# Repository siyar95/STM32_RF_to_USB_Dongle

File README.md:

# RF to USB Dongle – STM32L432 + nRF24L01

This project is a compact **RF-to-USB dongle** built using an **STM32L432KBU** microcontroller and an **nRF24L01** 2.4 GHz transceiver module.  
The device receives RF data wirelessly and transmits it to a host computer over USB.

## 🔧 Features

- **MCU**: STM32L432KBU (ARM Cortex-M4, ultra-low power)
- **RF Module**: nRF24L01 (2.4 GHz transceiver)
- **USB Interface**: Native USB device for communication with PC or host
- **SPI Interface**: Used to communicate with the nRF24L01
- **Low Power Operation**: Suitable for battery-powered wireless systems
- **Compact Design**: USB dongle-style form factor

## 🎯 Applications

- Wireless data receiver (e.g., for sensors, remotes)
- USB dongle for custom RF communication protocols
- PC bridge for STM32-based RF networks
- Debugging/logging tool for embedded wireless systems

## 🧱 PCB Details

- 4-layer PCB
- **Micro-USB (Type B)** connector
- On-board 3.3V LDO regulator for nRF24L01 and STM32
- SMA antenna

## 🧱 PCB Stackup

This project uses a 4-layer PCB for better signal integrity and power distribution:

1. **Top Layer (Layer 1)** – Signal  
2. **Inner Layer 1 (Layer 2)** – Ground (GND)  
3. **Inner Layer 2 (Layer 3)** – 3.3V Power Plane  
4. **Bottom Layer (Layer 4)** – Signal

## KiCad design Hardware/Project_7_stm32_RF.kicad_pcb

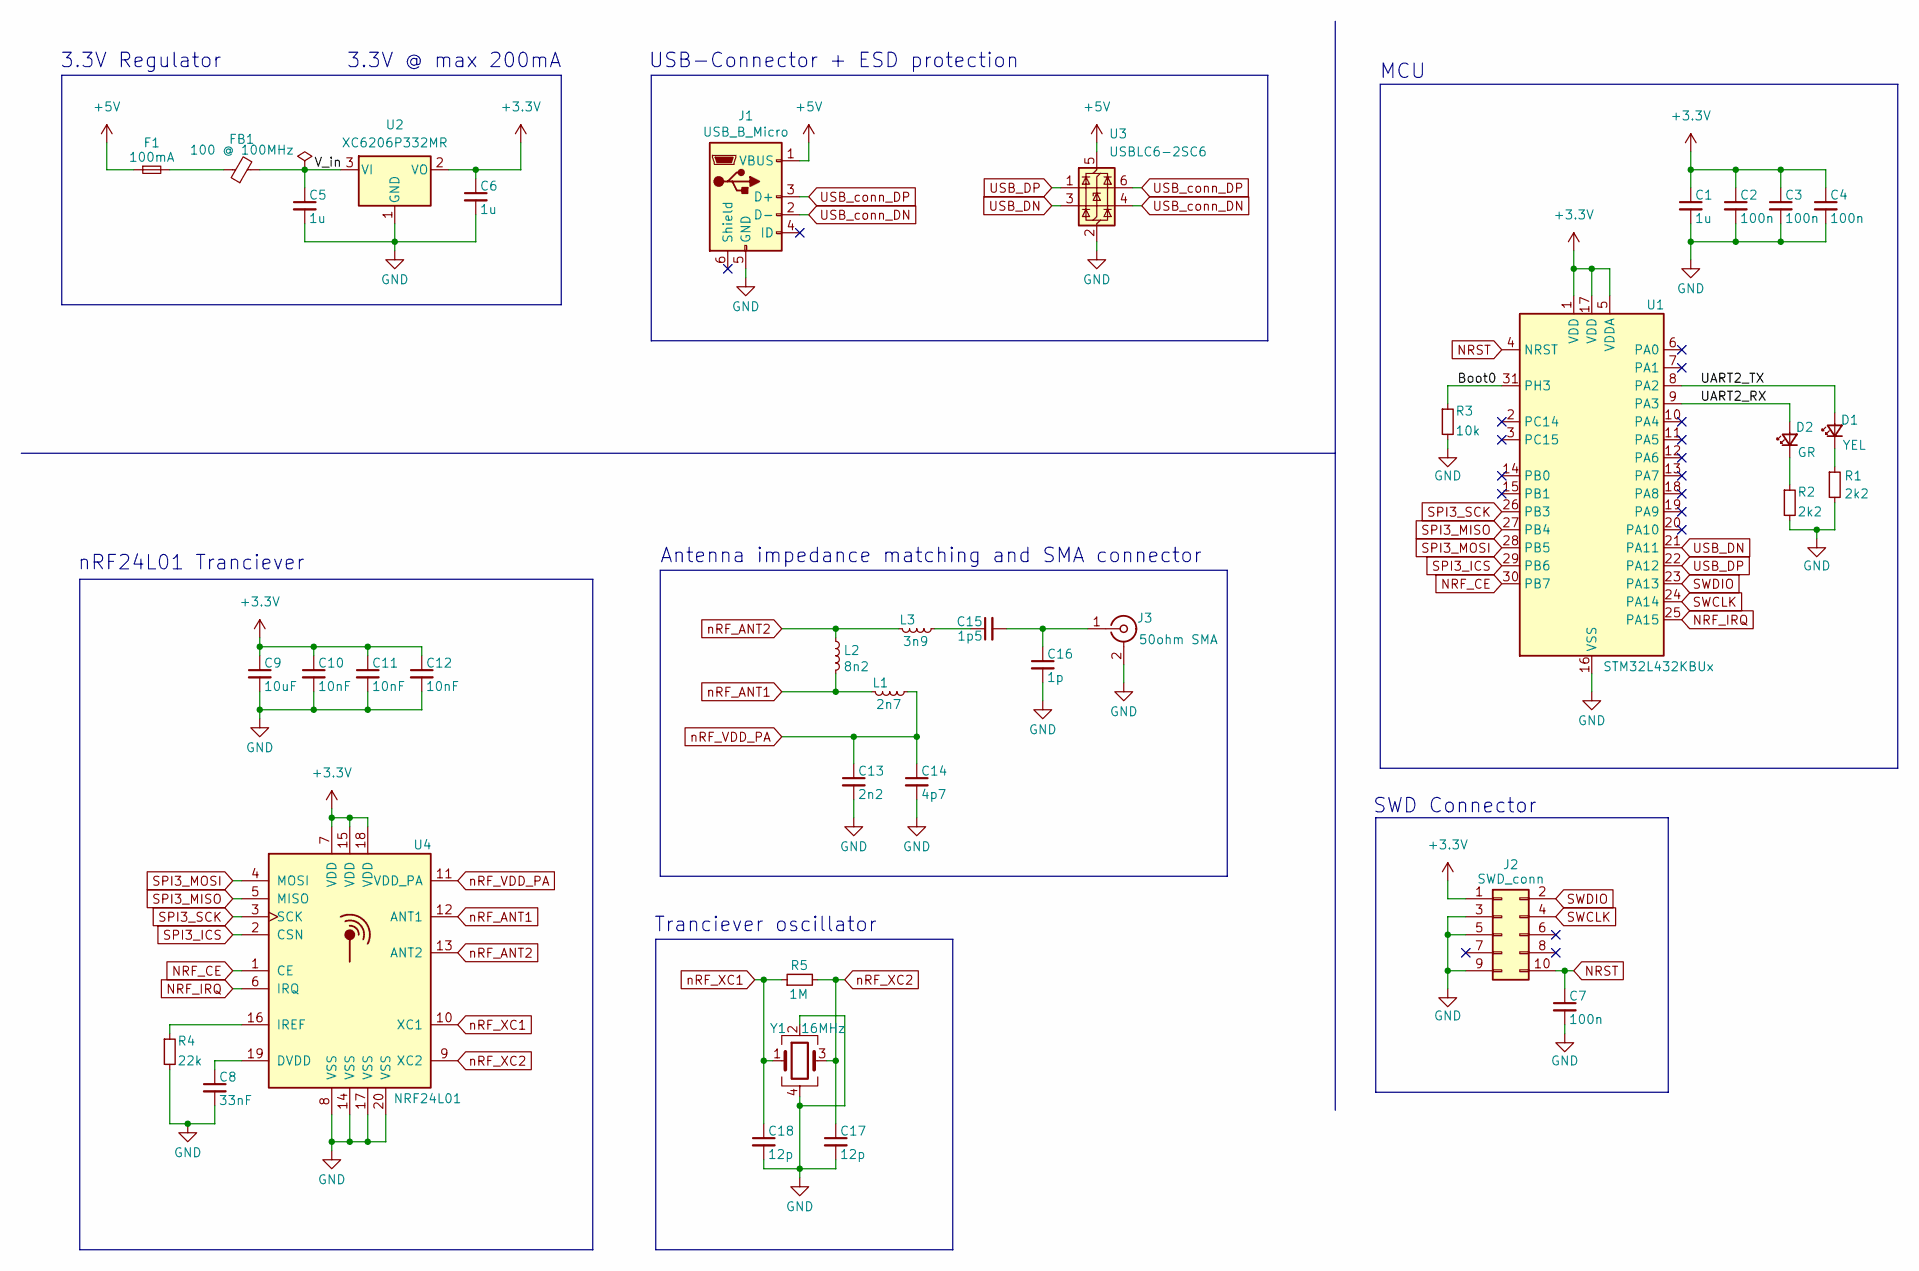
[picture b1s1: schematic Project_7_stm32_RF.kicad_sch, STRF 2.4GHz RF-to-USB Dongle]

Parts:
C1: 1u; C_0402_1005Metric
C2, C3, C4, C7: 100n; C_0402_1005Metric
C5, C6: 1u; C_0603_1608Metric
C8: 33nF; C_0402_1005Metric
C9: 10uF; C_0402_1005Metric
C10, C11, C12: 10nF; C_0402_1005Metric
C13: 2n2; C_0402_1005Metric
C14: 4p7; C_0402_1005Metric
C15: 1p5; C_0402_1005Metric
C16: 1p; C_0402_1005Metric
C17, C18: 12p; C_0402_1005Metric
D1: YEL; LED_0603_1608Metric
D2: GR; LED_0603_1608Metric
F1: 100mA; Fuse_1206_3216Metric
FB1: 100 @ 100MHz; L_0805_2012Metric
J1: USB_B_Micro; USB_Micro-B_Molex-105017-0001
J2: SWD_conn; PinHeader_2x05_P2.54mm_Vertical
J3: 50ohm SMA; SMA_Samtec_SMA-J-P-H-ST-EM1_EdgeMount
L1: 2n7; L_0402_1005Metric
L2: 8n2; L_0402_1005Metric
L3: 3n9; L_0402_1005Metric
R1, R2: 2k2; R_0603_1608Metric
R3: 10k; R_0402_1005Metric
R4: 22k; R_0402_1005Metric
R5: 1M; R_0402_1005Metric
U1: STM32L432KBUx; QFN-32-1EP_5x5mm_P0.5mm_EP3.45x3.45mm
U2: XC6206P332MR; SOT-23-3
U3: USBLC6-2SC6; SOT-23-6
U4: NRF24L01; QFN-20-1EP_4x4mm_P0.5mm_EP2.5x2.5mm
Y1: 16MHz; Crystal_SMD_3225-4Pin_3.2x2.5mm

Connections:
+3.3V: C1.1, C2.1, C3.1, C4.1, C6.1, C9.1, C10.1, C11.1, C12.1, J2.1, U1.1 (VDD), U1.5 (VDDA), U1.17 (VDD), U2.2 (VO), U4.7 (VDD), U4.15 (VDD), U4.18 (VDD); also elsewhere on the board
+5V: F1.1, J1.1 (VBUS), U3.5 (VBUS)
/Boot0: R3.1, U1.31 (PH3)
/UART2_RX: D2.2 (A), U1.9 (PA3)
/UART2_TX: D1.2 (A), U1.8 (PA2)
/V_in: C5.1, FB1.2, U2.3 (VI)
GND: C1.2, C2.2, C3.2, C4.2, C5.2, C6.2, C7.2, C8.2, C9.2, C10.2, C11.2, C12.2, C13.2, C14.2, C16.2, C17.2, C18.2, J1.5 (GND), J2.3, J2.5, J2.9, J3.2 (Ext), R1.2, R2.2, R3.2, R4.2, U1.16 (VSS), U1.32 (VSS), U1.33 (VSS), U2.1 (GND), U3.2 (GND), U4.8 (VSS), U4.14 (VSS), U4.17 (VSS), U4.20 (VSS), Y1.2, Y1.4; also elsewhere on the board
NRF_CE: U1.30 (PB7), U4.1 (CE)
NRF_IRQ: U1.25 (PA15), U4.6 (IRQ)
NRST: C7.1, J2.10, U1.4 (NRST); also elsewhere on the board
unnamed: C15.1, L3.1
unnamed: D1.1 (K), R1.1
unnamed: D2.1 (K), R2.1
unnamed: F1.2, FB1.1
unnamed 14: C15.2, C16.1, J3.1 (In); also elsewhere on the board
unnamed: C8.1, U4.19 (DVDD)
unnamed: R4.1, U4.16 (IREF)
SPI3_ICS: U1.29 (PB6), U4.2 (CSN)
SPI3_MISO: U1.27 (PB4), U4.5 (MISO)
SPI3_MOSI: U1.28 (PB5), U4.4 (MOSI)
SPI3_SCK: U1.26 (PB3), U4.3 (SCK)
SWCLK: J2.4, U1.24 (PA14); also elsewhere on the board
SWDIO: J2.2, U1.23 (PA13); also elsewhere on the board
USB_DN: U1.21 (PA11), U3.3 (I/O2)
USB_DP: U1.22 (PA12), U3.1 (I/O1)
USB_conn_DN: J1.2 (D-), U3.4 (I/O2)
USB_conn_DP: J1.3 (D+), U3.6 (I/O1)
nRF_ANT1: L1.2, L2.2, U4.12 (ANT1)
nRF_ANT2: L2.1, L3.2, U4.13 (ANT2)
nRF_VDD_PA: C13.1, C14.1, L1.1, U4.11 (VDD_PA)
nRF_XC1: C18.1, R5.1, U4.10 (XC1), Y1.1
nRF_XC2: C17.1, R5.2, U4.9 (XC2), Y1.3

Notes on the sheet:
SWD Connector
Antenna impedance matching and SMA connector
3.3V Regulator
MCU
3.3V @ max 200mA
nRF24L01 Tranciever
Tranciever oscillator
USB-Connector + ESD protection

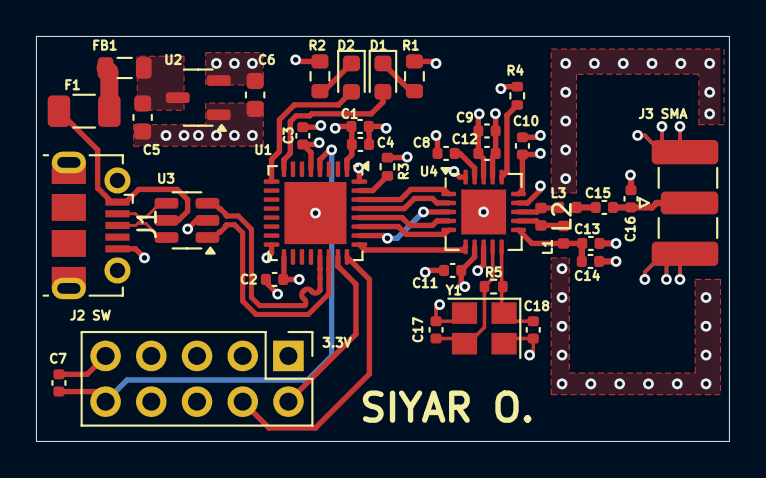
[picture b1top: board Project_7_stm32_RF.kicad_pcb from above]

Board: 4 copper layers, 38.5 x 22.5 mm, 38 parts (0 on the bottom side), 32 nets.

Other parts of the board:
J2 SW: SWD_conn; PinHeader_2x05_P2.54mm_Vertical
J3 SMA: 50ohm SMA; SMA_Samtec_SMA-J-P-H-ST-EM1_EdgeMount

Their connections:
+3.3V: J2 SW.1; also elsewhere on the board
GND: J2 SW.3, J2 SW.5, J2 SW.9, J3 SMA.2 (Ext); also elsewhere on the board
NRST: J2 SW.10; also elsewhere on the board
unnamed 14: J3 SMA.1 (In); also elsewhere on the board
SWCLK: J2 SW.4; also elsewhere on the board
SWDIO: J2 SW.2; also elsewhere on the board

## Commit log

2025-05-06 Rename Project_7_stm32_RF.kicad_pro to Hardware/Project_7_stm32_RF.kicad_pro
